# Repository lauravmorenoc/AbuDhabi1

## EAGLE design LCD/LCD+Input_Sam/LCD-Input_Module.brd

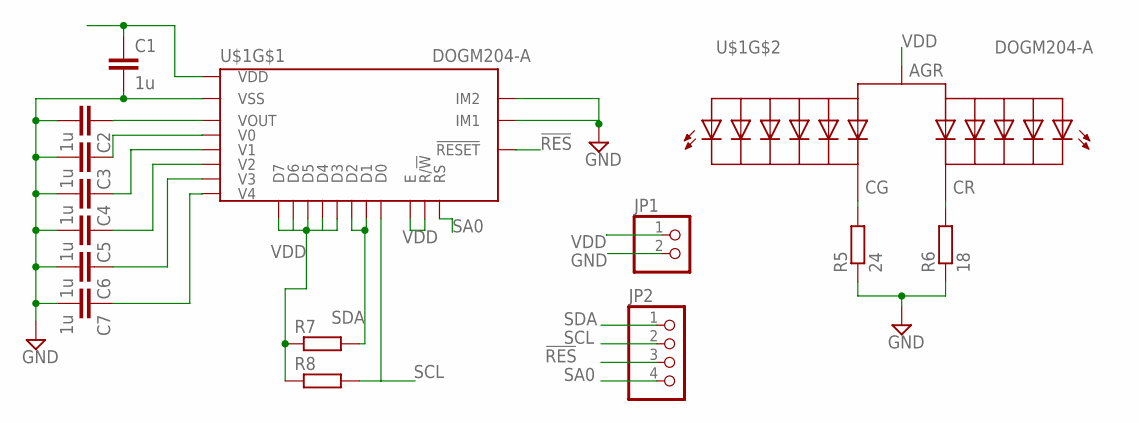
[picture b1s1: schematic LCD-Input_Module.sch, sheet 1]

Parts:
C1, C2, C3, C4, C5, C6, C7: 1u; C0603
JP1: PINHD-1X2; 1X02
JP2: PINHD-1X4; 1X04
R5: 24; R0603
R6: 18; R0603
R7, R8: R-EU_R0603; R0603
U$1: DOGM204-A; LCD

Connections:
!RES: JP2.3, U$1.P$44 (!RESET)
GND: C1.2, C2.2, C3.2, C4.2, C5.2, C6.2, C7.2, JP1.2, R5.1, R6.1, U$1.P$29 (IM2), U$1.P$30 (IM1), U$1.P$32 (VSS); also elsewhere on the board
unnamed: C3.1, U$1.P$24 (V0)
unnamed: C6.1, U$1.P$27 (V3)
unnamed: C4.1, U$1.P$25 (V1)
unnamed: C5.1, U$1.P$26 (V2)
unnamed: C7.1, U$1.P$28 (V4)
unnamed: C1.1, U$1.P$31 (VDD)
unnamed: C2.1, U$1.P$23 (VOUT)
unnamed: R5.2, U$1.P$21 (CG)
unnamed: R6.2, U$1.P$22 (CR)
SA0: JP2.4, U$1.P$43 (RS)
SCL: JP2.2, R8.2, U$1.P$40 (D0)
SDA: JP2.1, R7.2, U$1.P$38 (D2), U$1.P$39 (D1)
VDD: JP1.1, R7.1, R8.1, U$1.P$1 (AGR), U$1.P$33 (D7), U$1.P$34 (D6), U$1.P$35 (D5), U$1.P$36 (D4), U$1.P$37 (D3), U$1.P$41 (E), U$1.P$42 (R/!W); also elsewhere on the board

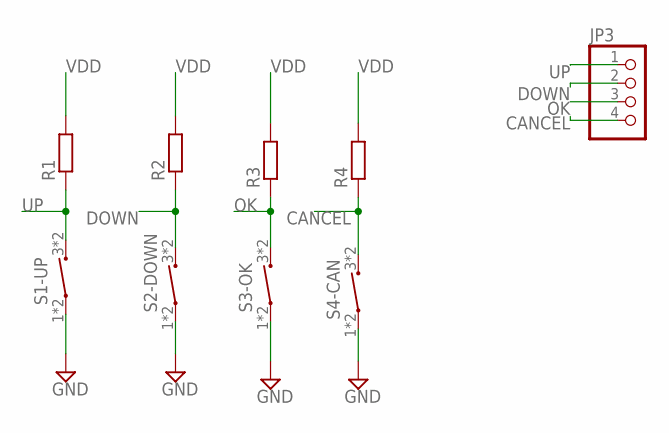
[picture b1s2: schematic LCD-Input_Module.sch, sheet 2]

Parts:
JP3: PINHD-1X4; 1X04
R1, R2, R3, R4: R-EU_R0603; R0603
S1-UP, S2-DOWN, S3-OK, S4-CAN: PTS647; PTS647-TACTSWITCH

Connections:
CANCEL: JP3.4, R4.1, S4-CAN.3 (2), S4-CAN.4 (2)
DOWN: JP3.2, R2.1, S2-DOWN.3 (2), S2-DOWN.4 (2)
GND: S1-UP.1, S1-UP.2 (1), S2-DOWN.1, S2-DOWN.2 (1), S3-OK.1, S3-OK.2 (1), S4-CAN.1, S4-CAN.2 (1); also elsewhere on the board
OK: JP3.3, R3.1, S3-OK.3 (2), S3-OK.4 (2)
UP: JP3.1, R1.1, S1-UP.3 (2), S1-UP.4 (2)
VDD: R1.2, R2.2, R3.2, R4.2; also elsewhere on the board

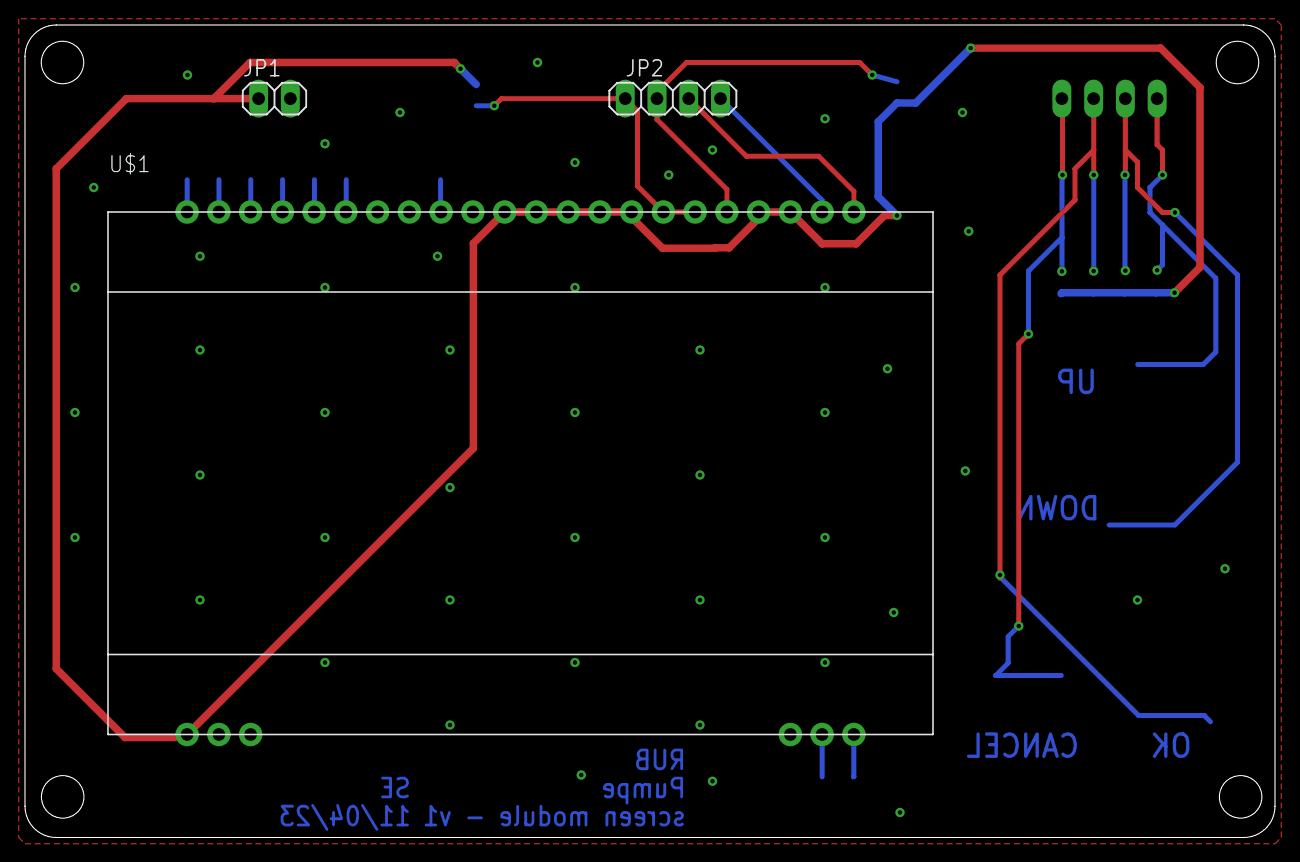
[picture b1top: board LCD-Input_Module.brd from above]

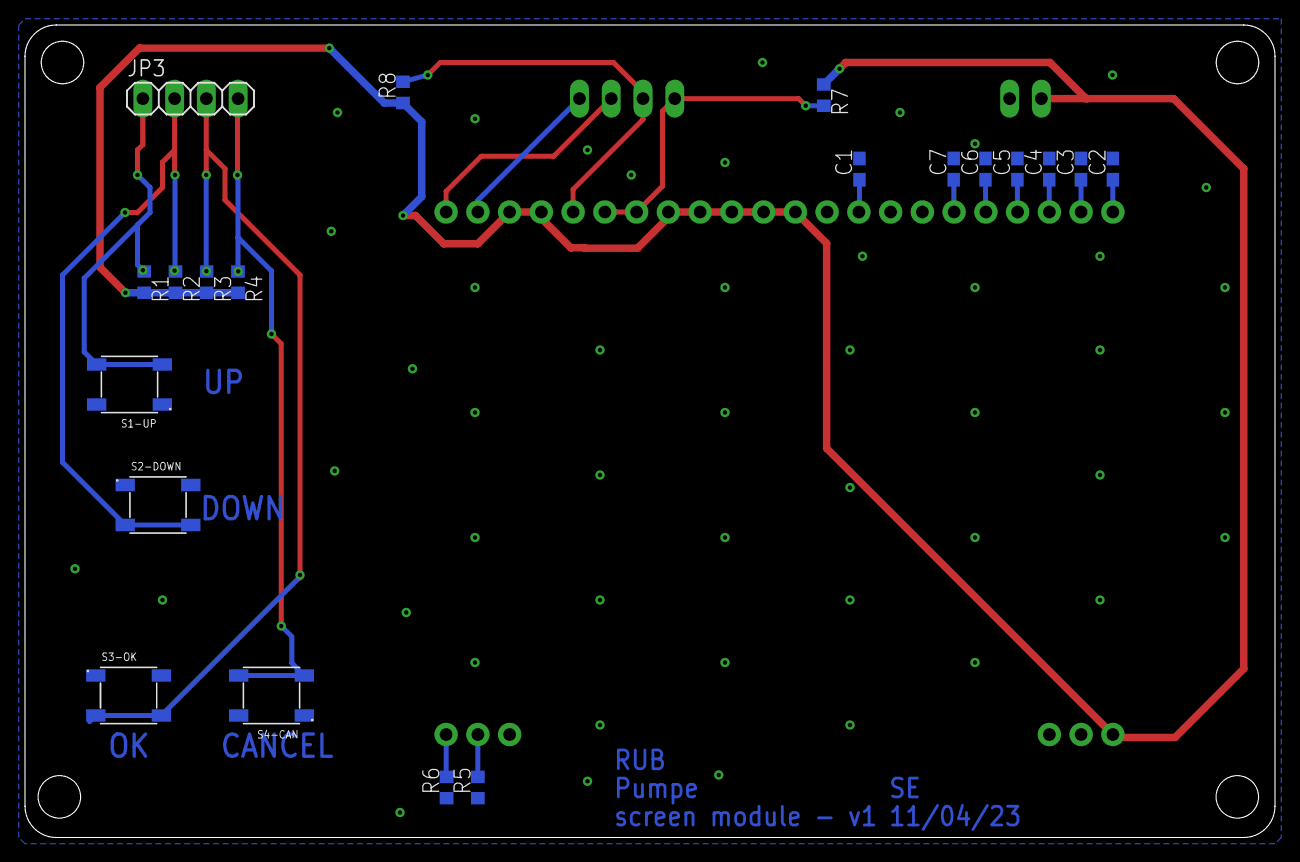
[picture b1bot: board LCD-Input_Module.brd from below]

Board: 2 copper layers, 100.0 x 65.0 mm, 23 parts (20 on the bottom side), 19 nets.

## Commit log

2023-09-19 First upload PCB
2023-09-19 Arduino Mega 2560 symbol and footprint adition
2023-09-19 Arduino Mega footpring change and LEDs addition
2023-09-25 A bit of order
2023-09-25 Nothing
2023-09-25 Routing part 1
2023-09-26 Everything routed and DRC checked and corrected, ready to print
2023-09-26 LCD screen update
2023-09-28 I2c address scanner code added
2023-10-09 LCD PCB Components mirror
2023-10-09 LCD PCB final touches
2023-10-16 RS232 und RS435 shields entfernt
2023-10-16 RS435 interface start
2023-10-18 RS232 interface changes (completed) and RS485 interface in working...
2023-10-20 LCD PCB changes according to Robins suggestions. Still pending one thing
2023-10-23 Just reading bout RS485
2023-10-24 Finally understood RS485
2023-10-25 LCD PCB finished (again)
2023-10-25 Some changes on the full PCB (Robin's folder). Ready to trace.
    All changes are being made (from now onwards) in Robins' folder (so it also keeps his changes).
2023-11-20 Main board file updated. Added Arduino code for the LCD
    The LCD is not working yet though.
2024-01-03 Merging branches
